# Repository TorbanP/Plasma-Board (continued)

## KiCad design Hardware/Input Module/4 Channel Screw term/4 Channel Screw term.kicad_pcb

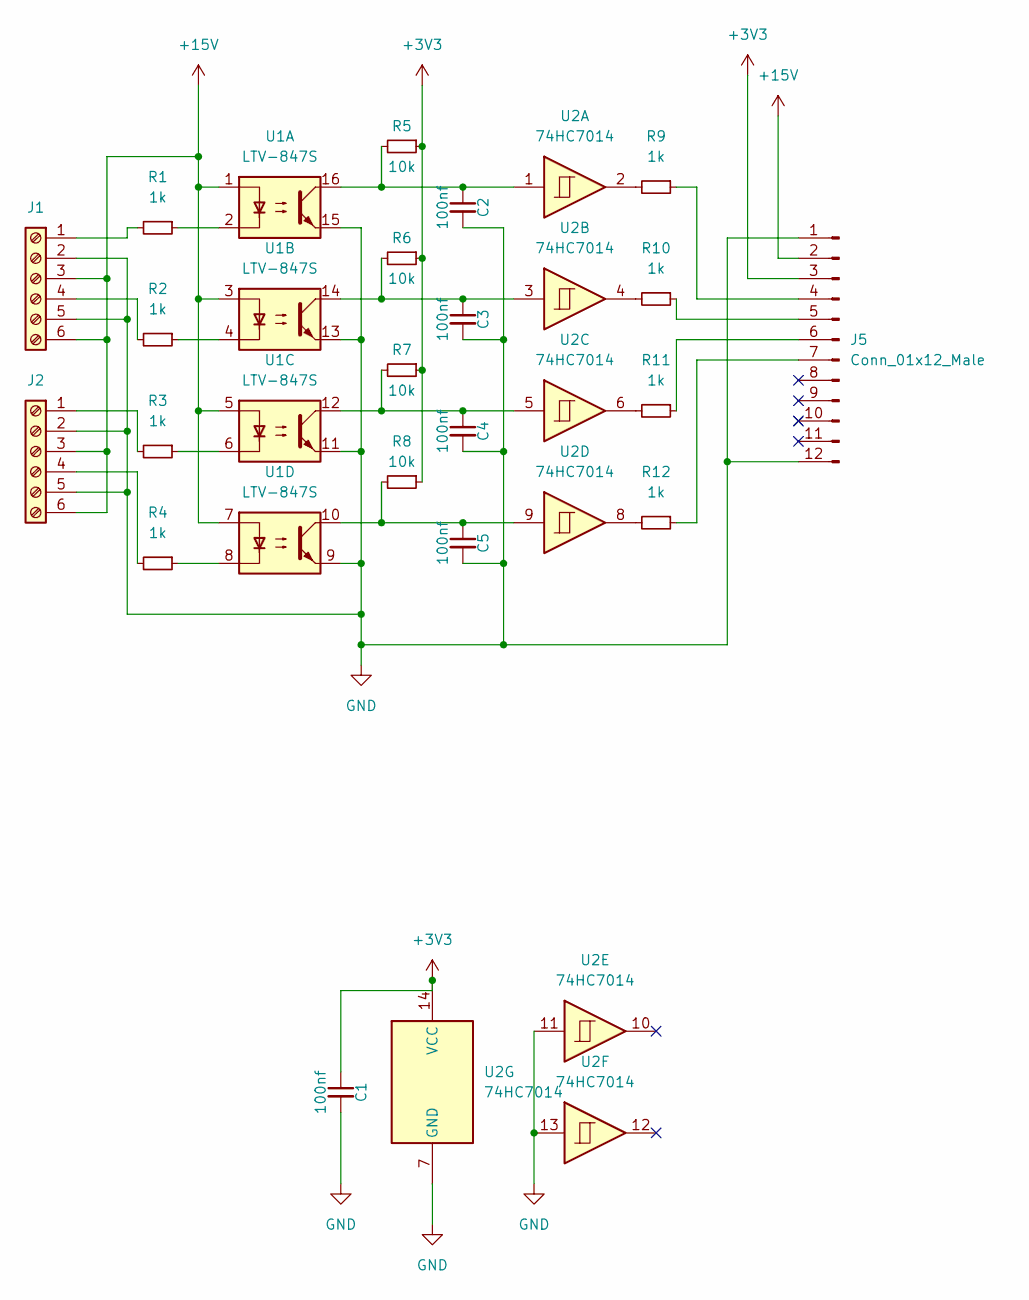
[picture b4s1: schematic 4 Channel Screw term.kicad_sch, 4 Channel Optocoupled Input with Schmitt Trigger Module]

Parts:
C1, C2, C3, C4, C5: 100nf; C_0603_1608Metric_Pad1.08x0.95mm_HandSolder
J1, J2: Screw_Terminal_01x06; 2x3 screw terminal3.5mm
J5: Conn_01x12_Male; PinHeader_1x12_P2.54mm_Vertical
R1, R2, R3, R4, R9, R10, R11, R12: 1k; R_0603_1608Metric_Pad0.98x0.95mm_HandSolder
R5, R6, R7, R8: 10k; R_0603_1608Metric_Pad0.98x0.95mm_HandSolder
U1: LTV-847S; SMDIP-16_W9.53mm
U2: 74HC7014; SO-14_3.9x8.65mm_P1.27mm

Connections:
+3V3: C1.1, J5.3, R5.1, R6.1, R7.1, R8.1, U2.14 (VCC)
+15V: J1.3, J1.6, J2.3, J2.6, J5.2, U1.1, U1.3, U1.5, U1.7
GND: C1.2, C2.2, C3.2, C4.2, C5.2, J1.2, J1.5, J2.2, J2.5, J5.1, J5.12, U1.9, U1.11, U1.13, U1.15, U2.7 (GND), U2.11, U2.13
unnamed: C2.1, R5.2, U1.16, U2.1
unnamed: C3.1, R6.2, U1.14, U2.3
unnamed: C4.1, R7.2, U1.12, U2.5
unnamed: C5.1, R8.2, U1.10, U2.9
unnamed: J1.1, R1.2
unnamed: J1.4, R2.2
unnamed: J2.1, R3.2
unnamed: J2.4, R4.2
unnamed: J5.4, R9.1
unnamed: J5.5, R10.1
unnamed: J5.6, R11.1
unnamed: J5.7, R12.1
unnamed: R1.1, U1.2
unnamed: R2.1, U1.4
unnamed: R3.1, U1.6
unnamed: R4.1, U1.8
unnamed: R9.2, U2.2
unnamed: R10.2, U2.4
unnamed: R11.2, U2.6
unnamed: R12.2, U2.8

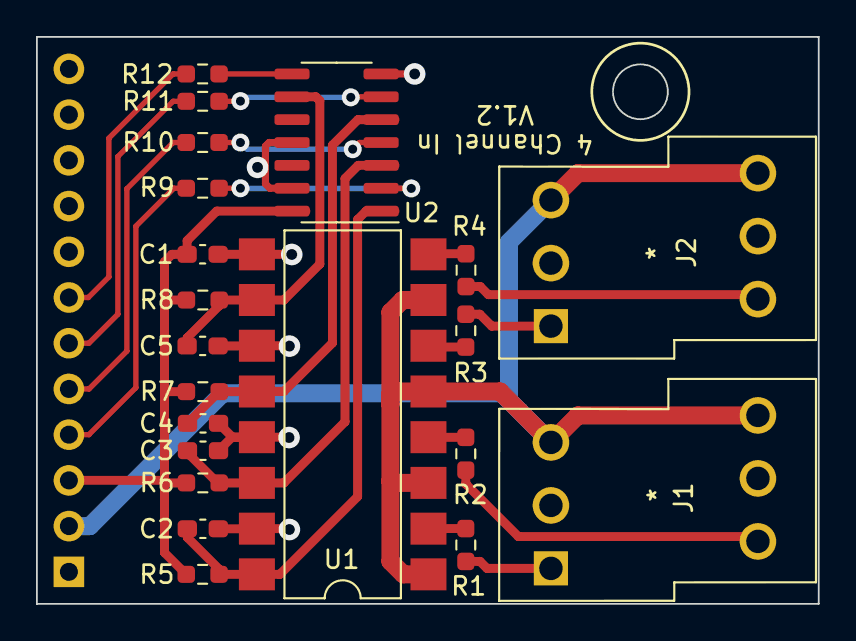
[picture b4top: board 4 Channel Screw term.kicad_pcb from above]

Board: 2 copper layers, 43.4 x 31.5 mm, 22 parts (1 on the bottom side), 23 nets.

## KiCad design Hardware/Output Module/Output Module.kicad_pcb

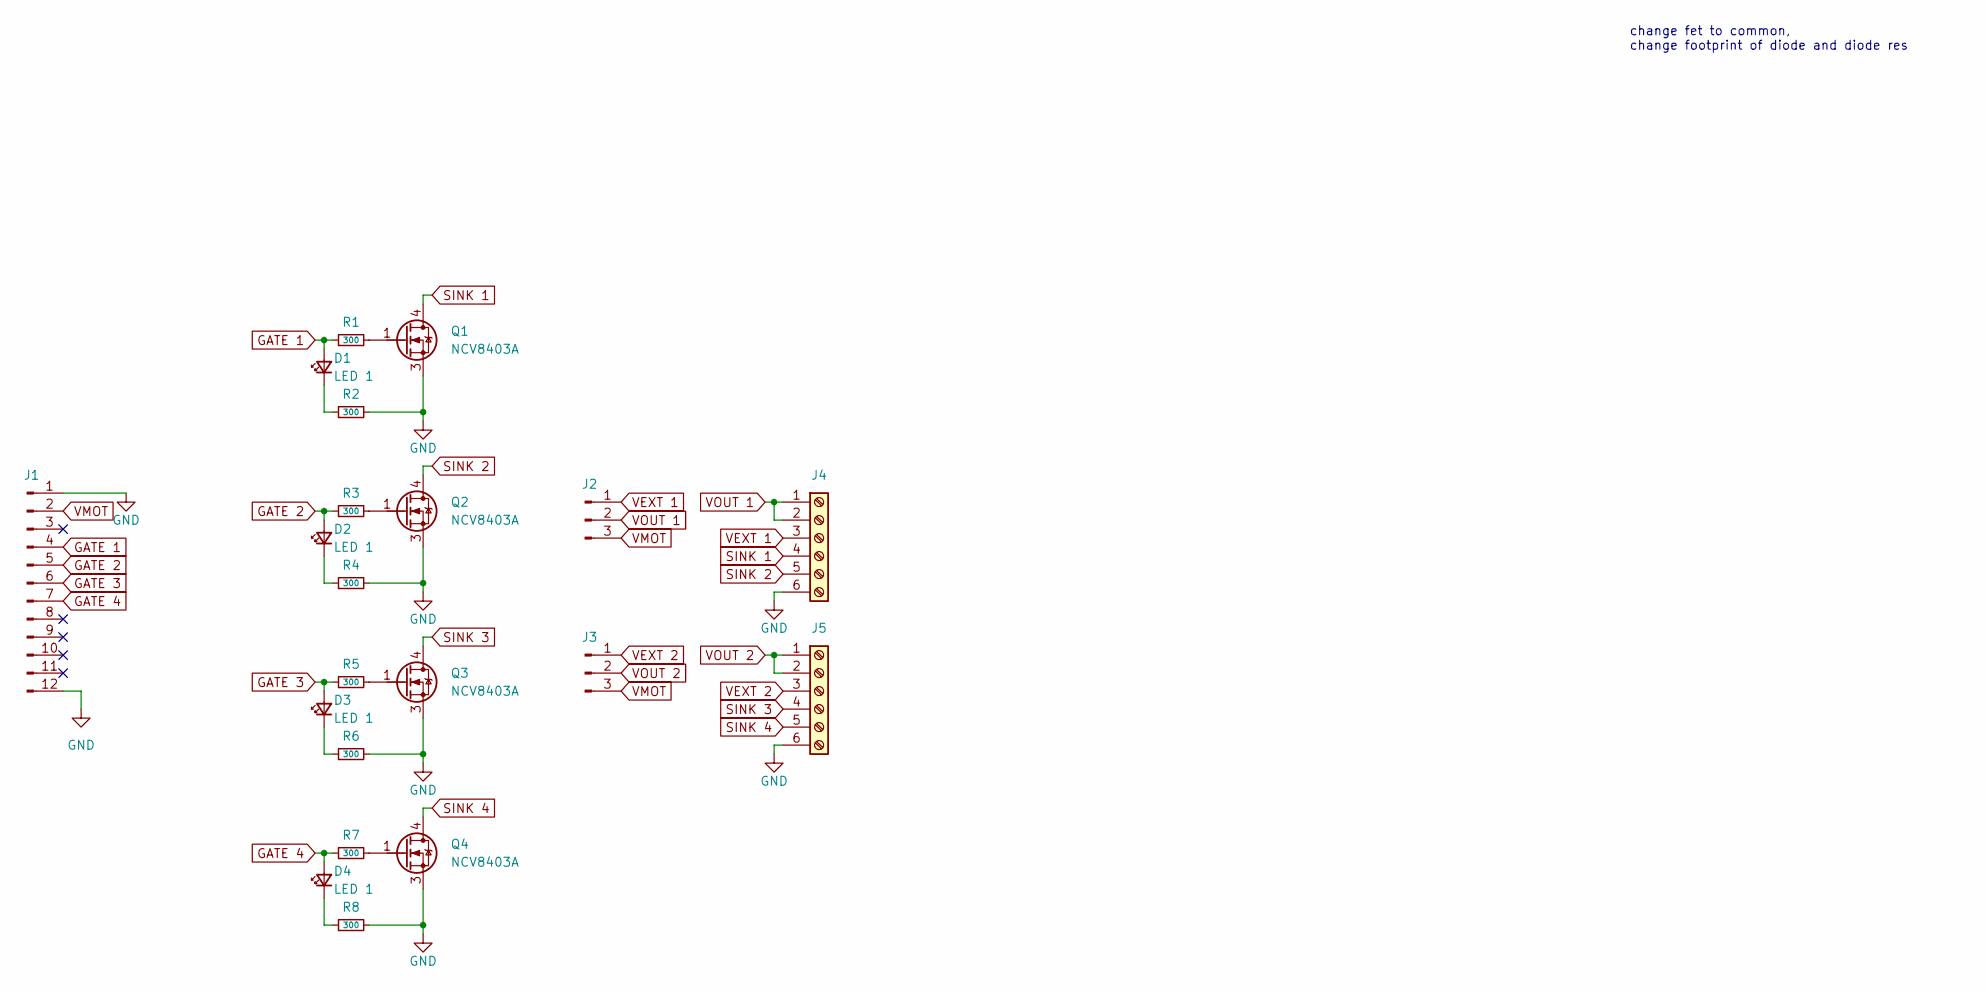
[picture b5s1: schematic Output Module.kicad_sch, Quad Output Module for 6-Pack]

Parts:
D1, D2, D3, D4: LED 1; LED_0603_1608Metric
J1: Conn_01x12_Male; PinHeader_1x12_P2.54mm_Vertical
J2, J3: Conn_01x03_Male; PinHeader_1x03_P2.54mm_Vertical
J4, J5: Screw_Terminal_01x06; 2x3 screw terminal3.5mm
Q1, Q2, Q3, Q4: NCV8403A; SOT-223
R1, R2, R3, R4, R5, R6, R7, R8: 300; R_0603_1608Metric

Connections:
GATE 1: D1.2 (A), J1.4, R1.1
GATE 2: D2.2 (A), J1.5, R3.1
GATE 3: D3.2 (A), J1.6, R5.1
GATE 4: D4.2 (A), J1.7, R7.1
GND: J1.1, J1.12, J4.6, J5.6, Q1.3 (S), Q2.3 (S), Q3.3 (S), Q4.3 (S), R2.2, R4.2, R6.2, R8.2
unnamed: D1.1 (K), R2.1
unnamed: D2.1 (K), R4.1
unnamed: D3.1 (K), R6.1
unnamed: D4.1 (K), R8.1
unnamed: Q1.1 (G), R1.2
unnamed: Q2.1 (G), R3.2
unnamed: Q3.1 (G), R5.2
unnamed: Q4.1 (G), R7.2
SINK 1: J4.4, Q1.4 (D)
SINK 2: J4.5, Q2.4 (D)
SINK 3: J5.4, Q3.4 (D)
SINK 4: J5.5, Q4.4 (D)
VEXT 1: J2.1, J4.3
VEXT 2: J3.1, J5.3
VMOT: J1.2, J2.3, J3.3
VOUT 1: J2.2, J4.1, J4.2
VOUT 2: J3.2, J5.1, J5.2

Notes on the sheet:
change fet to common, change footprint of diode and diode res

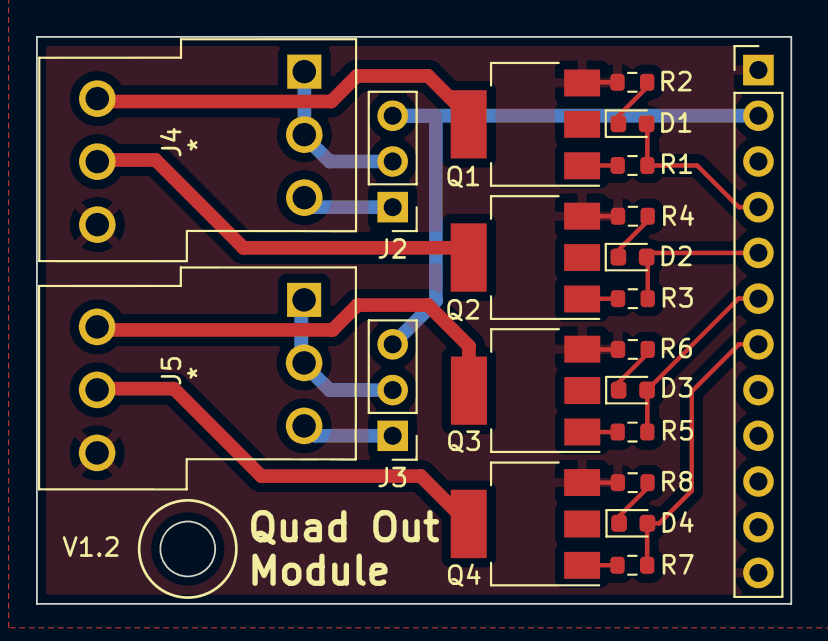
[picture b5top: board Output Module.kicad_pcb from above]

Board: 2 copper layers, 41.9 x 31.5 mm, 21 parts (0 on the bottom side), 22 nets.

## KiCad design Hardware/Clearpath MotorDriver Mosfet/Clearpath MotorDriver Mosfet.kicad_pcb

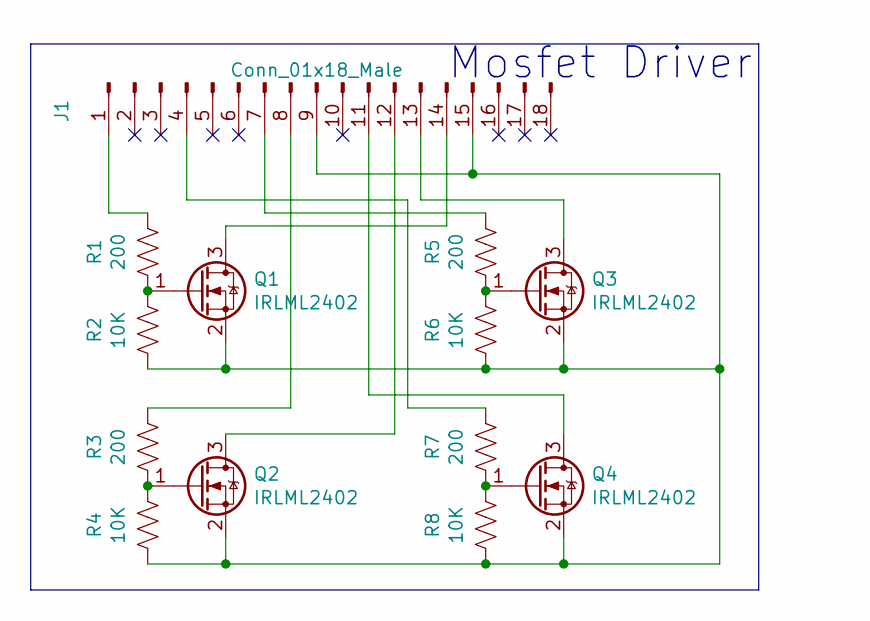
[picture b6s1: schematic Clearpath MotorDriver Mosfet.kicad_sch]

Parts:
J1: Conn_01x18_Male; ClearpathDriver
Q1, Q2, Q3, Q4: IRLML2402; SOT-23; LCSC C2588
R1, R3, R5, R7: 200; R_0603_1608Metric_Pad0.98x0.95mm_HandSolder; LCSC C125935
R2, R4, R6, R8: 10K; R_0603_1608Metric_Pad0.98x0.95mm_HandSolder; LCSC C144081

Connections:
unnamed: J1.1, R1.1
unnamed: J1.4, R7.1
unnamed: J1.7, R5.1
unnamed: J1.8, R3.1
unnamed: J1.11, Q4.3 (D)
unnamed: J1.12, Q2.3 (D)
unnamed: J1.13, Q3.3 (D)
unnamed: J1.14, Q1.3 (D)
unnamed: J1.9, J1.15, Q1.2 (S), Q2.2 (S), Q3.2 (S), Q4.2 (S), R2.2, R4.2, R6.2, R8.2
unnamed: Q1.1 (G), R1.2, R2.1
unnamed: Q2.1 (G), R3.2, R4.1
unnamed: Q3.1 (G), R5.2, R6.1
unnamed: Q4.1 (G), R7.2, R8.1

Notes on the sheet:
Mosfet Driver

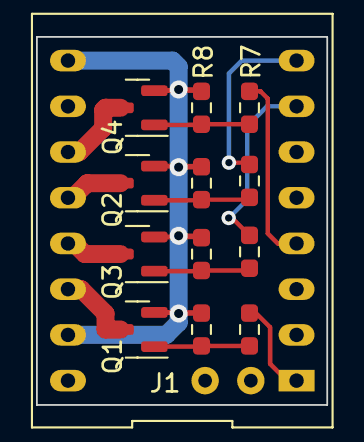
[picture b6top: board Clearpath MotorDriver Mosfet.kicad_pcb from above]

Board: 2 copper layers, 16.1 x 20.4 mm, 13 parts (0 on the bottom side), 13 nets.

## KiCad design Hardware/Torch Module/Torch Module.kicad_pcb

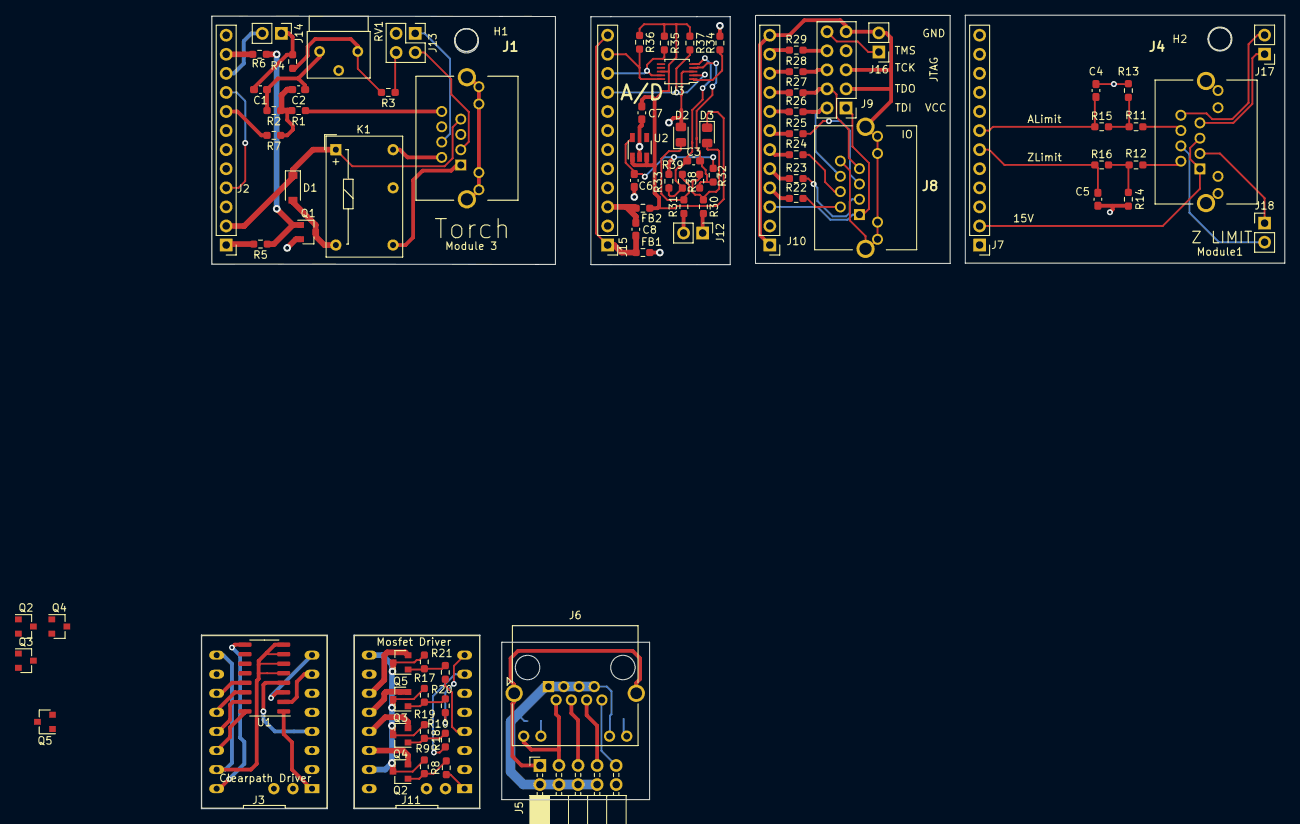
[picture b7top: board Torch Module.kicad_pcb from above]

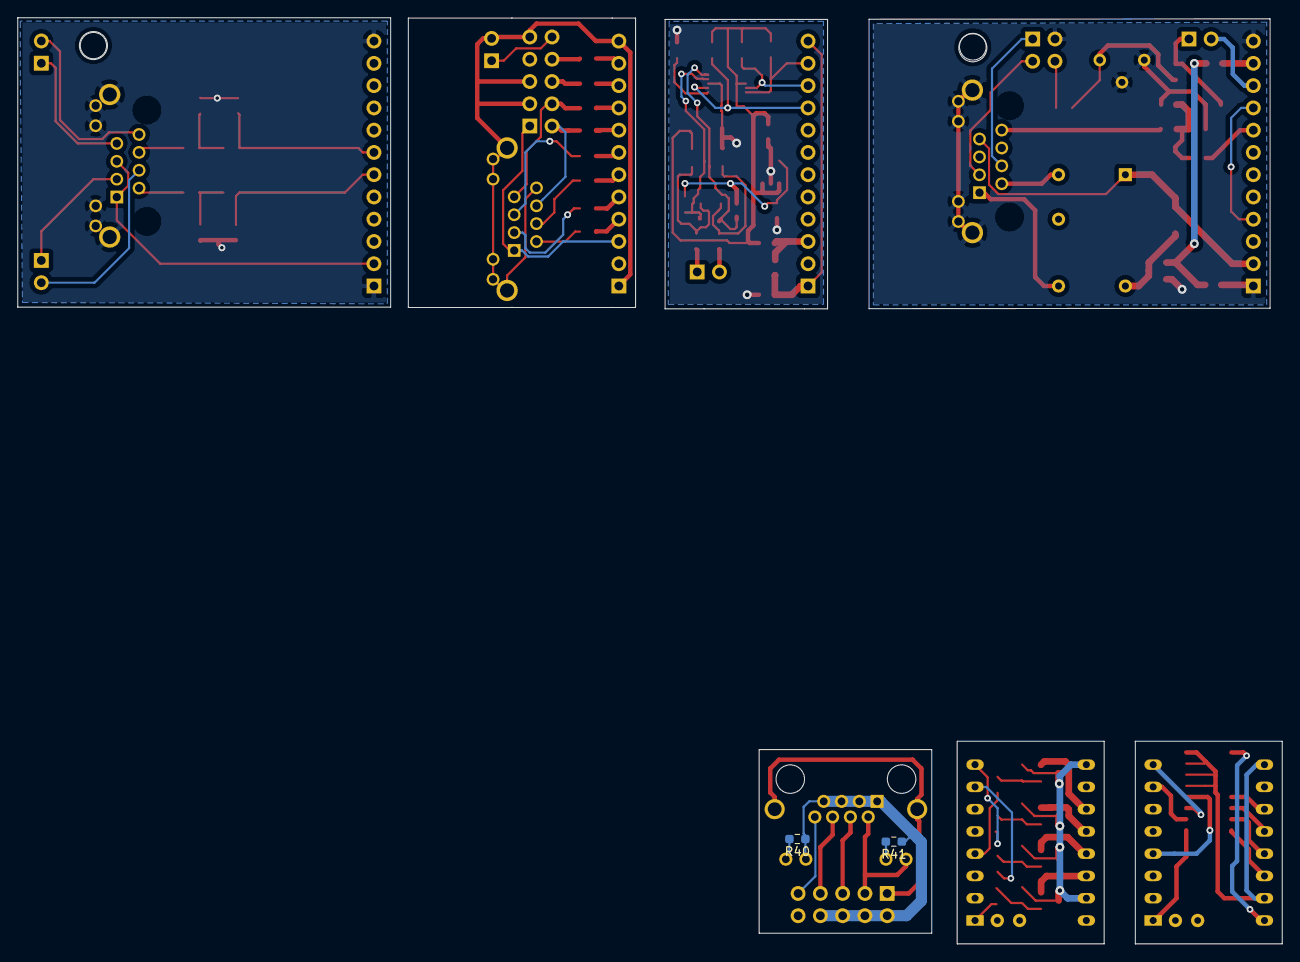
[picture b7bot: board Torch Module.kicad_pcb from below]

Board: 2 copper layers, 144.3 x 105.7 mm, 88 parts (2 on the bottom side), 94 nets.

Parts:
C1, C7: 100nf; C_0603_1608Metric_Pad1.08x0.95mm_HandSolder
C2, C4, C5, C6, C8: 1uf; C_0603_1608Metric_Pad1.08x0.95mm_HandSolder
C3: 22nf; C_0603_1608Metric_Pad1.08x0.95mm_HandSolder
D1: D; D_SOD-123
D2, D3: MSCD104H; D_0805_2012Metric_Pad1.15x1.40mm_HandSolder
FB1, FB2: BLM18HE152SN1D; R_0603_1608Metric_Pad0.98x0.95mm_HandSolder
H1, H2: MountingHole; MountingHole_3.2mm_M3
J1, J8: Torch; RJHSE3384
J2: Module3; PinHeader_1x12_P2.54mm_Vertical
J3, J11: Conn_01x18_Male; ClearpathDriver
J4: Limit; RJHSE3384
J5: PinSocket_2x05_P2.54mm_Horizontal
J6: 8P8C_LED_Shielded; RJ45_Amphenol_RJHSE538X
J7: Module1; PinHeader_1x12_P2.54mm_Vertical
J9: 2.54 pin; PinHeader_2x05_P2.54mm_Vertical
J10, J15: Module conn; PinHeader_1x12_P2.54mm_Vertical
J12, J14: Conn_01x02_Male; PinHeader_1x02_P2.54mm_Vertical
J13: PinHeader_2x02_P2.54mm_Vertical
J16, J17, J18: Reset; PinHeader_1x02_P2.54mm_Vertical
K1: G6E; Relay_SPDT_Omron_G6E
Q1, Q2, Q2#2, Q3, Q3#2, Q4, Q4#2, Q5, Q5#2: IRLML2402; SOT-23
R1, R3, R11, R12: 3.3K; R_0603_1608Metric_Pad0.98x0.95mm_HandSolder
R2, R13, R14, R30, R32, R33, R40, R41: 1K; R_0603_1608Metric_Pad0.98x0.95mm_HandSolder
R4, R5, R9, R15, R16, R17, R19, R21: 10K; R_0603_1608Metric_Pad0.98x0.95mm_HandSolder
R6, R7, R8, R10, R18, R20, R22, R23, R24, R25, R26, R27, R28, R29, R38, R39: 200; R_0603_1608Metric_Pad0.98x0.95mm_HandSolder
R31: 2K; R_0603_1608Metric_Pad0.98x0.95mm_HandSolder
R34, R35, R36, R37: 2.4K; R_0603_1608Metric_Pad0.98x0.95mm_HandSolder
RV1: 2K; Potentiometer_Bourns_3339S_Horizontal
U1: ULN2002; SO-16_3.9x9.9mm_P1.27mm
U2: NCV8114ASN150T1G; TSOT-23-5
U3: ADS1115IDGS; TSSOP-10_3x3mm_P0.5mm

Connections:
unnamed: C1.1, C2.1, J1.9, J1.10, J1.11, J1.12, J1.MH1, J1.MH2, J2.1, J2.12, J13.3, Q1.2, R2.2, R5.2, RV1.1, RV1.2
unnamed: C1.2, J14.1, R4.1
unnamed: C2.2, R1.2, R2.1, R7.1
unnamed: C3.1, R32.2, R38.1, U3.4
unnamed: C3.2, R33.1, R39.1, U3.5
unnamed: C4.1, C5.1, J4.9, J4.10, J4.11, J4.12, J4.MH1, J4.MH2, J7.1, J7.12, R13.2, R14.2
unnamed: C4.2, J7.7, R15.1
unnamed: C5.2, J7.6, R16.1
unnamed: C6.1, R32.1, R33.2, U2.5
unnamed: C6.2, C7.2, D2.2, FB1.2, R34.2, U2.2, U3.3
unnamed: C7.1, D3.1, FB2.1, R35.1, R36.1, R37.1, U2.1, U2.3, U3.8
unnamed: C8.1, FB2.2, J15.3
unnamed: C8.2, FB1.1, J15.1, J15.12
unnamed: D1.1, J1.7, J2.2, K1.1
unnamed: D1.2, K1.6, Q1.3
unnamed: D2.1, R31.2, R39.2
unnamed: D3.2, R30.1, R38.2
unnamed: J1.1, K1.7
unnamed: J1.2, K1.12
unnamed: J1.3, J13.2
unnamed: J1.4, J13.1
unnamed: J1.8, R1.1
unnamed: J2.4, J2.9
unnamed: J2.8, R7.2
unnamed: J2.11, R6.1
unnamed: J3.1, U1.1
unnamed: J3.4, U1.4
unnamed: J3.7, U1.2
unnamed: J3.8, U1.3
unnamed: J3.11, U1.13
unnamed: J3.12, U1.14
unnamed: J3.13, U1.15
unnamed: J3.14, U1.16
unnamed: J3.9, J3.15, U1.5, U1.6, U1.7, U1.8
unnamed: J3.16, U1.9
unnamed: J4.1, J4.5, J7.2
unnamed: J4.2, R12.1
unnamed: J4.6, R11.1
unnamed: J5.1, J6.SH
unnamed: J5.2, J5.4, J5.6, J5.8, J6.1, J6.3, J6.5, J6.7, J6.11, R40.1, R41.1
unnamed: J5.3, J6.2, J6.9
unnamed: J5.5, J6.4
unnamed: J5.7, J6.6
unnamed: J5.9, J6.8
unnamed: J6.10, R41.2
unnamed: J6.12, R40.2
unnamed: J8.2, R22.2
unnamed: J8.3, R23.2
unnamed: J8.4, R24.2
unnamed: J8.5, R25.2
unnamed: J8.6, J9.2, R26.2
unnamed: J8.7, J9.4, R27.2
unnamed: J9.6, R28.2
unnamed: J9.8, R29.2
unnamed: J8.8, J8.9, J8.10, J8.11, J8.12, J8.MH1, J8.MH2, J9.3, J9.5, J9.9, J10.1, J10.12, J16.2
unnamed: J8.1, J9.1, J10.3
unnamed: J10.4, R22.1
unnamed: J10.5, R23.1
unnamed: J10.6, R24.1
unnamed: J10.7, R25.1
unnamed: J10.8, R26.1
unnamed: J10.9, R27.1
unnamed: J10.10, R28.1
unnamed: J10.11, R29.1
unnamed: J11.1, R8.1
unnamed: J11.4, R20.1
unnamed: J11.7, R18.1
unnamed: J11.8, R10.1
unnamed: J11.11, Q5.3, Q5#2.2
unnamed: J11.12, Q3.3, Q3#2.2
unnamed: J11.13, Q4.3, Q4#2.2
unnamed: J11.14, Q2.3, Q2#2.2
unnamed: J11.9, J11.15, Q2.2, Q2#2.3, Q3.2, Q3#2.3, Q4.2, Q4#2.3, Q5.2, Q5#2.3, R9.2, R17.2, R19.2, R21.2
unnamed: J12.1, R30.2
unnamed: J12.2, R31.1
unnamed: J13.4, R3.1
unnamed: J2.10, J14.2
unnamed: J15.9, R37.2, U3.2
unnamed: J15.10, R35.2, U3.9
unnamed: J15.11, R36.2, U3.10
unnamed: J9.10, J16.1
unnamed: J4.7, J17.1
unnamed: J4.8, J17.2
unnamed: J4.3, J18.1
unnamed: J4.4, J18.2
unnamed: Q1.1, R5.1, R6.2
unnamed: Q2.1, Q2#2.1, R8.2, R9.1
unnamed: Q3.1, Q3#2.1, R10.2, R17.1
unnamed: Q4.1, Q4#2.1, R18.2, R19.1
unnamed: Q5.1, Q5#2.1, R20.2, R21.1
unnamed: R3.2, R4.2, RV1.3
unnamed: R11.2, R13.1, R15.2
unnamed: R12.2, R14.1, R16.2
unnamed: R34.1, U3.1

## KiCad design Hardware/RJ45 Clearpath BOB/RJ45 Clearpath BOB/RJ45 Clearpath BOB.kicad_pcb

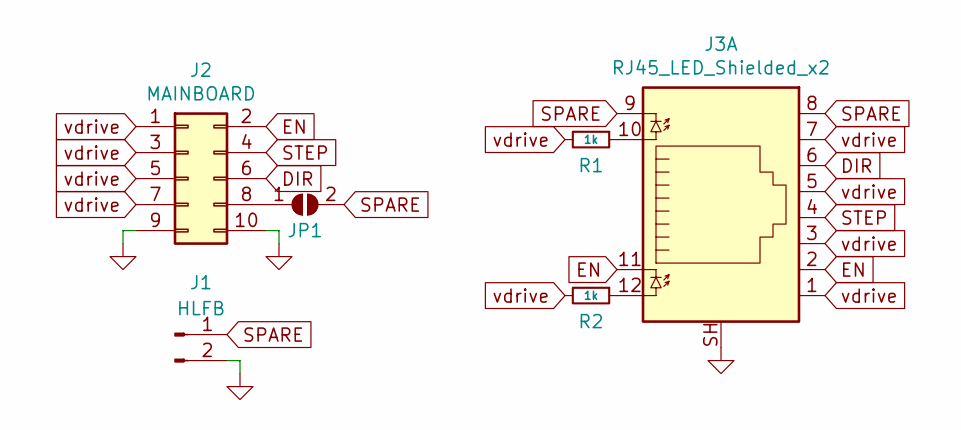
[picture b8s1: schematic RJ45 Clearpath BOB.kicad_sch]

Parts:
J1: HLFB; PinHeader_1x02_P2.54mm_Vertical
J2: MAINBOARD; PinHeader_2x05_P2.54mm_Horizontal
J3: RJ45_LED_Shielded_x2; RJ45_Amphenol_RJHSE538X
JP1: SolderJumper_2_Open; SolderJumper-2_P1.3mm_Open_TrianglePad1.0x1.5mm
R1, R2: 1k; R_0603_1608Metric

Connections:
DIR: J2.6, J3.6
EN: J2.2, J3.2, J3.11
GND: J1.2, J2.9, J2.10, J3.SH
unnamed: J2.8, JP1.1 (A)
unnamed: J3.10, R1.1
unnamed: J3.12, R2.1
SPARE: J1.1, J3.8, J3.9, JP1.2 (B)
STEP: J2.4, J3.4
vdrive: J2.1, J2.3, J2.5, J2.7, J3.1, J3.3, J3.5, J3.7, R1.2, R2.2

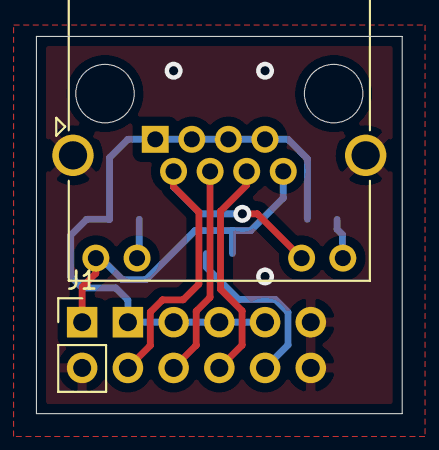
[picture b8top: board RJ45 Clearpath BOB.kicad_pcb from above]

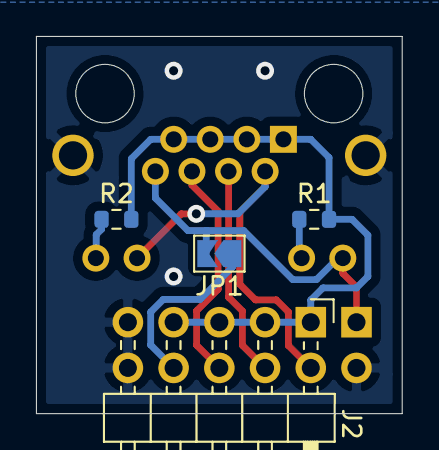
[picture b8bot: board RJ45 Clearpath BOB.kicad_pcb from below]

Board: 2 copper layers, 20.3 x 21.0 mm, 6 parts (4 on the bottom side), 9 nets.

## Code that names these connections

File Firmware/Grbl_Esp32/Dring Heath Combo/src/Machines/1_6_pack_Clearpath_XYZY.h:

#pragma once
// clang-format off

/*
    6_pack_extrenal_XYYZ_1SWXYZ_2SWHSRP_3MosfetMistFlood_4_10VSpin.h

    Covers all V1 versions V1p0, V1p1, etc

    Part of Grbl_ESP32
    Pin assignments for the ESP32 I2S 6-axis board
    
    2020-10-7 B. Dring for David M.

    Grbl_ESP32 is free software: you can redistribute it and/or modify
    it under the terms of the GNU General Public License as published by
    the Free Software Foundation, either version 3 of the License, or
    (at your option) any later version.
    Grbl is distributed in the hope that it will be useful,
    but WITHOUT ANY WARRANTY; without even the implied warranty of
    MERCHANTABILITY or FITNESS FOR A PARTICULAR PURPOSE.  See the
    GNU General Public License for more details.
    You should have received a copy of the GNU General Public License
    along with Grbl_ESP32.  If not, see <http://www.gnu.org/licenses/>.
*/
#define MACHINE_NAME            "1Our 6 Pack External XYYZ"

#define N_AXIS 3

// === Special Features

// I2S (steppers & other output-only pins)
#define USE_I2S_OUT
#define USE_I2S_STEPS
//#define DEFAULT_STEPPER ST_I2S_STATIC

//#define USE_STEPSTICK   // makes sure MS1,2,3 !reset and !sleep are set

#define I2S_OUT_BCK             GPIO_NUM_22
#define I2S_OUT_WS              GPIO_NUM_17
#define I2S_OUT_DATA            GPIO_NUM_21


//#define X_STEPPER_MS3           I2SO(3)   // X_CS
//#define Y_STEPPER_MS3           I2SO(6)   // Y_CS
//#define Y2_STEPPER_MS3          I2SO(11)  // Z_CS
//#define Z_STEPPER_MS3           I2SO(14)  // A_CS

//#define STEPPER_RESET           GPIO_NUM_19

// Motor Socket #1
#define X_DISABLE_PIN           I2SO(0)
#define X_DIRECTION_PIN         I2SO(1)
#define X_STEP_PIN              I2SO(2)

// Motor Socket #2
#define Y_DISABLE_PIN           I2SO(4)
#define Y_DIRECTION_PIN         I2SO(5)
#define Y_STEP_PIN              I2SO(6)


// Motor Socket #4
#define Y2_DISABLE_PIN           I2SO(12)
#define Y2_DIRECTION_PIN         I2SO(13)
#define Y2_STEP_PIN              I2SO(14)

// Motor Socket #3
#define Z_DIRECTION_PIN         I2SO(15)
#define Z_STEP_PIN              I2SO(1)
#define Z_DISABLE_PIN           I2SO(2)
//Socket I/O reference
// === Default settings
#define DEFAULT_STEP_PULSE_MICROSECONDS I2S_OUT_USEC_PER_PULSE

// Module in Socket #1
// Dring Heath Controller\Kicad\Dring Heath Small\Torch Module\Torch Module.sch

#define Z_LIMIT_PIN             GPIO_NUM_35   // hard Z limit
#define PROBE_PIN               GPIO_NUM_34  //soft Z limit
//#define DEFAULT_INVERT_PROBE_PIN        0

// Module in socket #3
#define SPINDLE_TYPE            SpindleType::RELAY // default, check actual $Spindle/Type Setting
#define SPINDLE_OUTPUT_PIN      GPIO_NUM_26 // Handover Z axis contol to THCIO32
//#define COOLANT_MIST_PIN       GPIO_NUM_26
//#define COOLANT_FLOOD_PIN      GPIO_NUM_4
//#define SPINDLE_TYPE            SpindleType::LASER
//#define DEFAULT_LASER_MODE      1
#define CONTROL_FEED_HOLD_PIN       GPIO_NUM_36 //from THC IO pin 33 jumper Climit and Blimit to THC
#define CONTROL_CYCLE_START_PIN     GPIO_NUM_39  // see control switches in wiki
//#define CONTROL_RESET_PIN           GPIO_NUM_36

/*
    Socket I/O reference
    The list of modules is here...
    https://github.com/bdring/6-Pack_CNC_Controller/wiki/CNC-I-O-Module-List
    Click on each module to get example for using the modules in the sockets


Socket #1
#1 GPIO_NUM_33 
#2 GPIO_NUM_32
#3 GPIO_NUM_35 (input only)
#4 GPIO_NUM_34 (input only)

Socket #2
#1 GPIO_NUM_2
#2 GPIO_NUM_25
#3 GPIO_NUM_39 (input only)
#4 GPIO_NUM_36 (input only)

Socket #3
#1 GPIO_NUM_26
#2 GPIO_NUM_4
#3 GPIO_NUM_16
#4 GPIO_NUM_27

Socket #4
#1 GPIO_NUM_14
#2 GPIO_NUM_13
#3 GPIO_NUM_15
#4 GPIO_NUM_12

Socket #5
#1 I2SO(24)  (output only)
#2 I2SO(25)  (output only)
#3 I2SO26)  (output only)

*/



// 4x Switch Input module  in socket #2
//#define CONTROL_FEED_HOLD_PIN       GPIO_NUM_2
//#define CONTROL_CYCLE_START_PIN     GPIO_NUM_25
//#define CONTROL_RESET_PIN           GPIO_NUM_39
//#define PROBE_PIN                   GPIO_NUM_36


// Quad MOSFET module in socket #3
// https://github.com/bdring/6-Pack_CNC_Controller/wiki/Quad-MOSFET-Module
//#define COOLANT_MIST_PIN       GPIO_NUM_26
//#define COOLANT_FLOOD_PIN      GPIO_NUM_4

// 0-10V Spindle in socket #4
// https://github.com/bdring/6-Pack_CNC_Controller/wiki/0-10V-Output-Module
//#define SPINDLE_TYPE            SpindleType::_10V// default, check actual $Spindle/Type Setting
//#define SPINDLE_OUTPUT_PIN      GPIO_NUM_14
//#define SPINDLE_FORWARD_PIN     GPIO_NUM_13
//#define SPINDLE_REVERSE_PIN     GPIO_NUM_15

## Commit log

2021-01-01 Add folder structure and CAM PCB Files
2021-01-04 Add Existing Kicad Files, Add BDRING, Start new schematic
2021-01-11 Update CAM files
2021-01-22 Cam Upload
2021-01-22 test commit
2021-01-23 Started routing main board
2021-01-23 more routing and added Dring large folder
2021-01-24 more routing
2021-01-24 Routing
    needs 2 Jumper wires 18v in and 15v
2021-01-25 Main and Module Boards Routed
2021-01-26 BOM and Machine.h file
2021-01-27 Updated BOM
    added Connector pin outs and Order of operation on another sheet
2021-01-28 Pin changes
    Put RJ45 connector on Jtag module for more IO put Pot on Torch module to
    adjust Plasma voltage
2021-01-28 Updated pin numbers
2021-01-28 added files to Grbl_Esp32 for VScode
2021-01-28 Made workspace for vscode
2021-02-01 Change to BOM
    Shifted a few tracks changed 3.3v reg to 1A
2021-02-02 Added mosfet motor driver
2021-02-02 Changed voltage divider for THC input
2021-02-02 put protection resistors on JTAG module
2021-02-03 Tidied module boards
2021-02-04 2mm border around modules and tabs
2021-02-04 Panalized Module boards with tabs
2021-02-04 mounting hole in module board
2021-02-05 fixed voltage divider for THC
2021-02-06 Added external A/D ADS1115
2021-02-07 routed a/d board
    put simulation on excel bom
2021-02-07 added A/D to panel
2021-02-09 Torch1Module.sch alternate A/D input
2021-02-10 Modified clamped A/D input updates panalized boards
2021-02-10 Changed RJ45 conector on motor driver module
2021-02-10 removed an edge cut
2021-02-13 changed reset circuit on ESP 32s and driver board gerber
2021-02-13 Updated torch module boards for external reset
2021-03-10 Update main board schematic to pass erc. reorganize
2021-03-10 Gerbers for Main Board, minimal DRC errors
2021-03-10 Corrected jumper wire mark layer
2021-03-10 fix all erc and drc, add lcsc pns, fix rj45, fix footprints
2021-03-13 Ordered parts, finished modules, fixed rj45
2021-11-07 Added RJ45 Clearpath BOB, minor torch module footprint fix
2021-11-07 Added fluidnc
2021-11-07 Update old files from Cam USB
2021-11-07 removed fluidNC, use his git instead
2021-11-09 Updated THC 11/7/21
    updated THC
2021-11-12 Updates to config and Excel
2021-11-18 gerbers for clearpath bob, lcsc order
2021-11-20 added a test gcode file
    added a test gcode file
2021-11-21 updated config.yaml
    probe and Z limit active low
2021-12-01 Cleanup files
    Clean up
2022-02-05 Added Quad input and Output Modules
    Input and Output modules
2022-02-05 BOM forInput Output Modules
    BOM LCSC and Aliexpress
2022-02-06 Fixed Mosfet footprint on Clearpath driver
2022-02-08 Main Board Updater V1.2
2022-03-20 Gerber Upload Ordered version
2022-03-27 update footprints, cad model for plastic clip
2022-04-11 board holder plus ibom
2022-04-17 redesigned input and output modules, cleaned some files, ordered 10 of each
2022-08-27 Random changes
2022-11-07 Changes to THC EXT A-D
2022-11-08 Changes to THC Ext A-D
    Torch read active HIGH
2022-11-09 updated a-d conector pins
2022-11-12 Add CAD files
2022-11-19 Updates from Nov 11
2022-11-20 Updates 2022-11-20
2022-11-21 THC handover updates
2022-11-26 Added THC readme and THC GUI.tft
2022-12-10 add plasma cable connection, move and rename design file
2022-12-11 Firmware Cleanup
2022-12-11 Add project for THC test code
2022-12-11 Add OTA base code
2022-12-13 Porting code, and cleaning up
2022-12-13 More code cleanup
2022-12-21 Add Hypertherm douments
2023-02-26 Changes to pin mapping
2023-02-26 Connection Sheet update
2023-02-28 sheetcam example gcode
2023-02-28 add ipt example part for testing
2023-03-10 Start 2.0 board with onboard esp32 with antennas
2023-03-10 Remove junk backups
2023-03-10 Add start of stepper outputs, add usb to serial bits, start renaming things
2023-03-10 USB added, working on esp32 basic passives
2023-03-11 Work on shift registers, and power for esp32
2023-03-11 Level shifters for motors roughed in, discover V1.1 issues with overcurrent on outputs
2023-03-11 Organize, add mux, mapping and figuring out modules
2023-03-11 Cleanup, add decoupling resistors
2023-03-11 add comments for power supplies
2023-03-11 add prototypes for most of BDrings modules
2023-03-11 Added Dring CNC Modules
2023-03-12 add smps for 5v and 12v, add more module prototypes
2023-03-12 add leds to smps
2023-03-13 redesigned 5v psu to more modern chip. start working on lcsc pn's
2023-03-13 tweaking
2023-03-13 create a generic reference design for modules
2023-03-13 designing expansion modules
2023-03-13 updated comments for further changes, add uart
2023-03-15 Setup and start code for THC 2.0
2023-03-15 Basic code complete
2023-03-15 Bugfixing, made more robust
2023-03-15 add pierce retry via boot, and led blink on idle mechanism
2023-03-15 remove isr led on off. esp32 panics if we get stuck in an isr so no need
2023-03-16 fix reset pierce bug
2023-03-16 add gpio12 warning
2023-03-16 Pin Mapping update
2023-03-17 Pin Naming Changes
2023-03-20 Update for secondary pin for pierce, simplify
2023-03-21 Create March2023.code-workspace
2023-03-27 add post processor, tune code for new pinouts. add comments for 2.0
2023-04-18 progress updates
2023-04-19 Documentation add
2023-04-19 add code to disable plasma if no start signal received in good time. add ADC code to print voltage during running
2023-04-20 basic non thc working code
2023-05-26 v2 work
2023-09-30 start a teensy version with migration to grblHAL for built in THC
2023-11-17 Add iosender
2025-10-15 update files
2025-10-15 add postprocessors and test gcode
